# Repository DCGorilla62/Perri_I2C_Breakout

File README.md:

# Perri_I2C_Breakout

Prototype board to connect all Perri boards for testing

Would use OSHPark services to spin this board.

Double copper layer. Black PCB.

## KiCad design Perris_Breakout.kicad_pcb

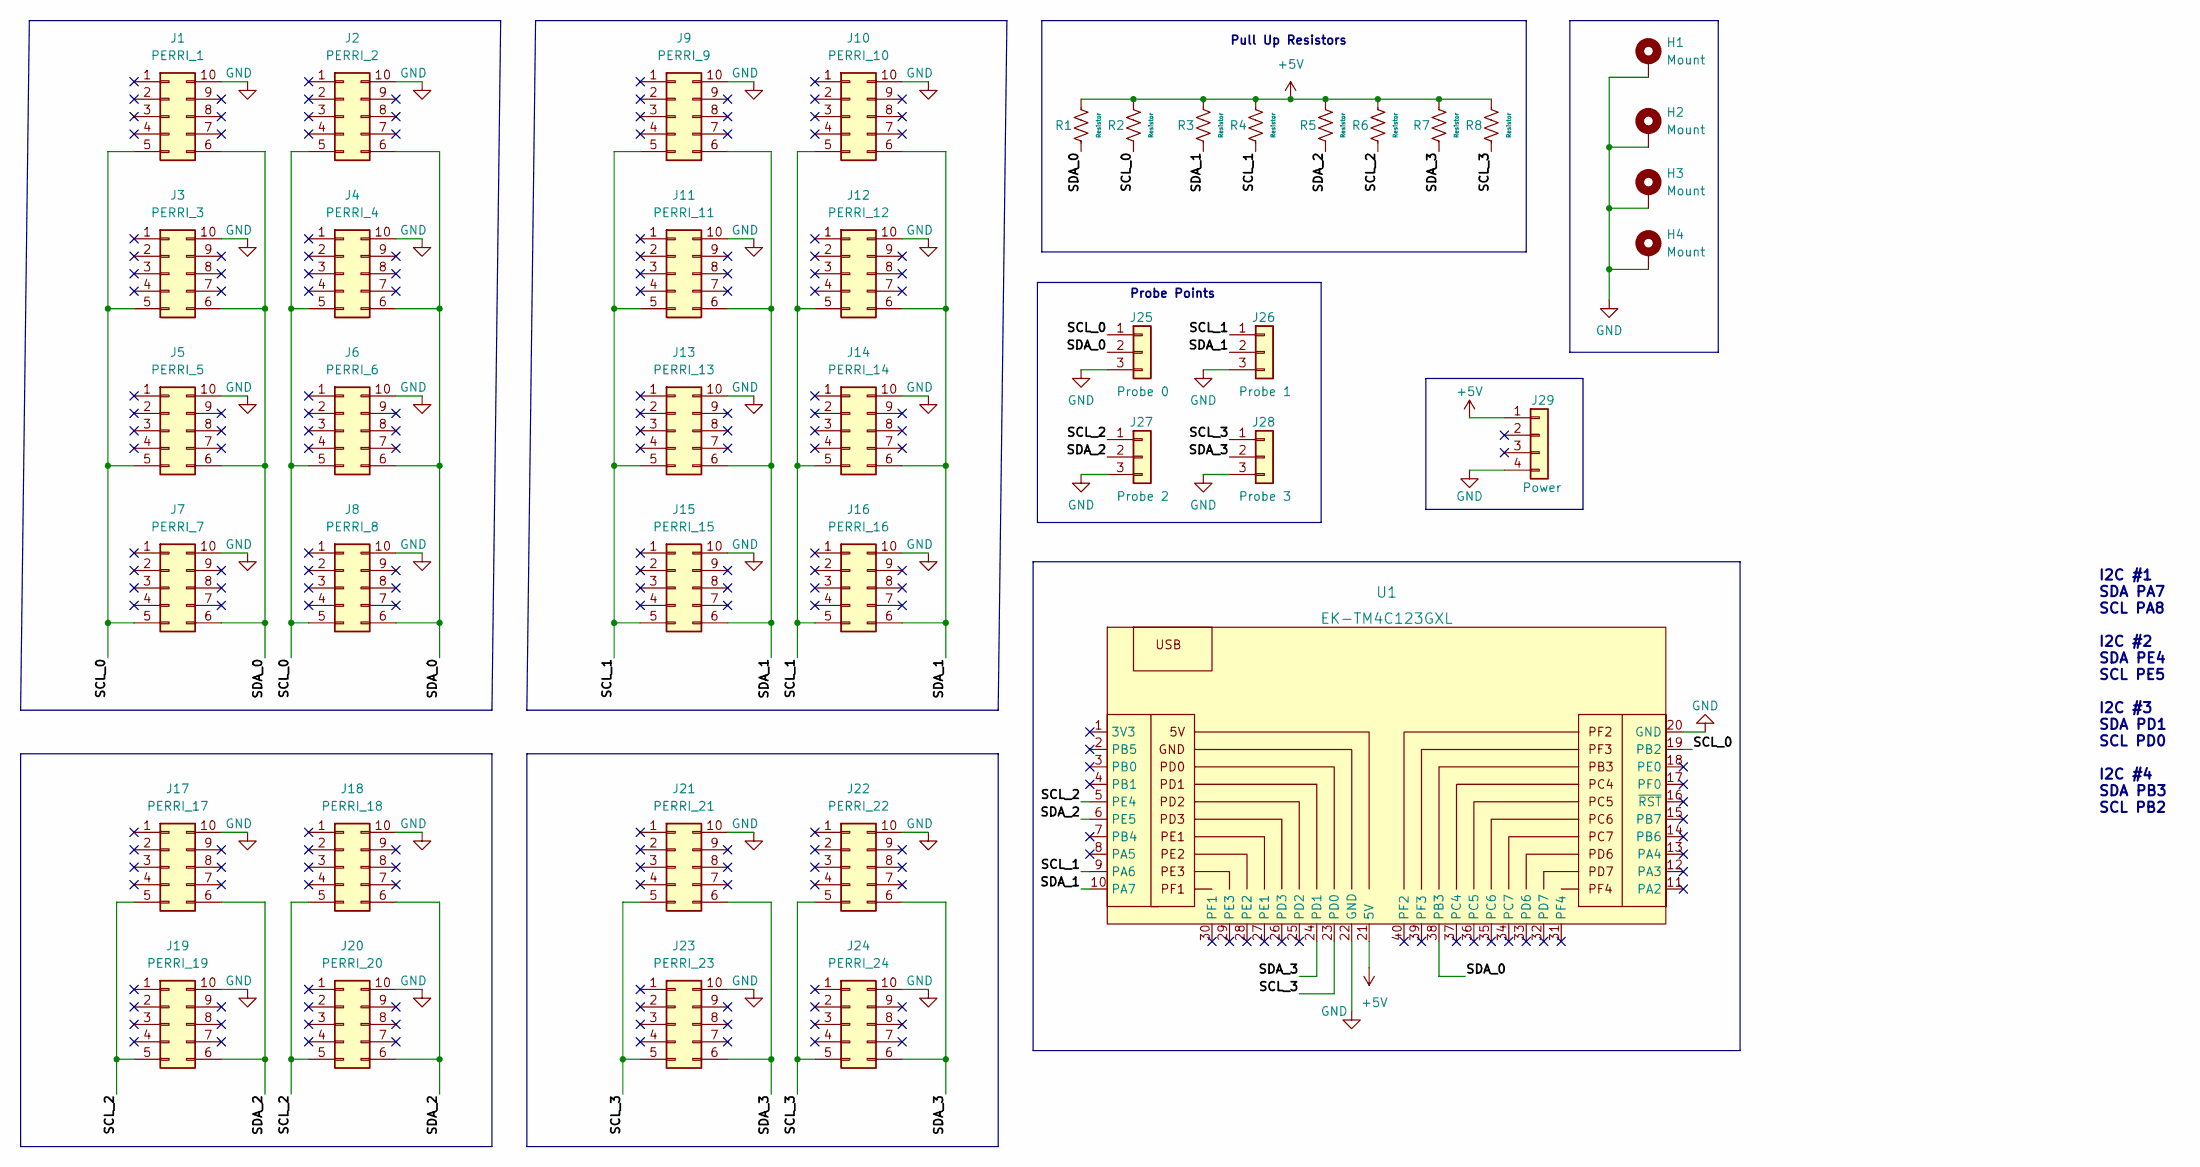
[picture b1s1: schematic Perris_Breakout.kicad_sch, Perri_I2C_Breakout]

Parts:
H1, H2, H3, H4: Mount; MountingHole_3.2mm_M3_ISO7380_Pad
J1: PERRI_1; Perri_conn_2x5_Reverse
J2: PERRI_2; Perri_conn_2x5_Reverse
J3: PERRI_3; Perri_conn_2x5_Reverse
J4: PERRI_4; Perri_conn_2x5_Reverse
J5: PERRI_5; Perri_conn_2x5_Reverse
J6: PERRI_6; Perri_conn_2x5_Reverse
J7: PERRI_7; Perri_conn_2x5_Reverse
J8: PERRI_8; Perri_conn_2x5_Reverse
J9: PERRI_9; Perri_conn_2x5_Reverse
J10: PERRI_10; Perri_conn_2x5_Reverse
J11: PERRI_11; Perri_conn_2x5_Reverse
J12: PERRI_12; Perri_conn_2x5_Reverse
J13: PERRI_13; Perri_conn_2x5_Reverse
J14: PERRI_14; Perri_conn_2x5_Reverse
J15: PERRI_15; Perri_conn_2x5_Reverse
J16: PERRI_16; Perri_conn_2x5_Reverse
J17: PERRI_17; Perri_conn_2x5_Reverse
J18: PERRI_18; Perri_conn_2x5_Reverse
J19: PERRI_19; Perri_conn_2x5_Reverse
J20: PERRI_20; Perri_conn_2x5_Reverse
J21: PERRI_21; Perri_conn_2x5_Reverse
J22: PERRI_22; Perri_conn_2x5_Reverse
J23: PERRI_23; Perri_conn_2x5_Reverse
J24: PERRI_24; Perri_conn_2x5_Reverse
J25: Probe 0; PinHeader_1x03_P2.54mm_Vertical
J26: Probe 1; PinHeader_1x03_P2.54mm_Vertical
J27: Probe 2; PinHeader_1x03_P2.54mm_Vertical
J28: Probe 3; PinHeader_1x03_P2.54mm_Vertical
J29: Power; Molex_Micro-Fit_3.0_43650-0400_1x04_P3.00mm_Horizontal
R1, R2, R3, R4, R5, R6, R7, R8: Resistor; R_0805_2012Metric
U1: EK-TM4C123GXL; TM4C123GXL_launchpad_male_connector; MPN EK-TM4C123GXL

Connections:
+5V: J29.1, R1.2, R2.2, R3.2, R4.2, R5.2, R6.2, R7.2, R8.2, U1.21 (5V)
/SCL_0: J1.5, J2.5, J3.5, J4.5, J5.5, J6.5, J7.5, J8.5, J25.1, R2.1, U1.19 (PB2)
/SCL_1: J9.5, J10.5, J11.5, J12.5, J13.5, J14.5, J15.5, J16.5, J26.1, R4.1, U1.9 (PA6)
/SCL_2: J17.5, J18.5, J19.5, J20.5, J27.1, R6.1, U1.5 (PE4)
/SCL_3: J21.5, J22.5, J23.5, J24.5, J28.1, R8.1, U1.23 (PD0)
/SDA_0: J1.6, J2.6, J3.6, J4.6, J5.6, J6.6, J7.6, J8.6, J25.2, R1.1, U1.38 (PB3)
/SDA_1: J9.6, J10.6, J11.6, J12.6, J13.6, J14.6, J15.6, J16.6, J26.2, R3.1, U1.10 (PA7)
/SDA_2: J17.6, J18.6, J19.6, J20.6, J27.2, R5.1, U1.6 (PE5)
/SDA_3: J21.6, J22.6, J23.6, J24.6, J28.2, R7.1, U1.24 (PD1)
GND: H1.1, H2.1, H3.1, H4.1, J1.10, J2.10, J3.10, J4.10, J5.10, J6.10, J7.10, J8.10, J9.10, J10.10, J11.10, J12.10, J13.10, J14.10, J15.10, J16.10, J17.10, J18.10, J19.10, J20.10, J21.10, J22.10, J23.10, J24.10, J25.3, J26.3, J27.3, J28.3, J29.4, U1.20 (GND), U1.22 (GND)

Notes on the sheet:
Probe Points
Pull Up Resistors
I2C #1 SDA PA7 SCL PA8 I2C #2 SDA PE4 SCL PE5 I2C #3 SDA PD1 SCL PD0 I2C #4 SDA PB3 SCL PB2

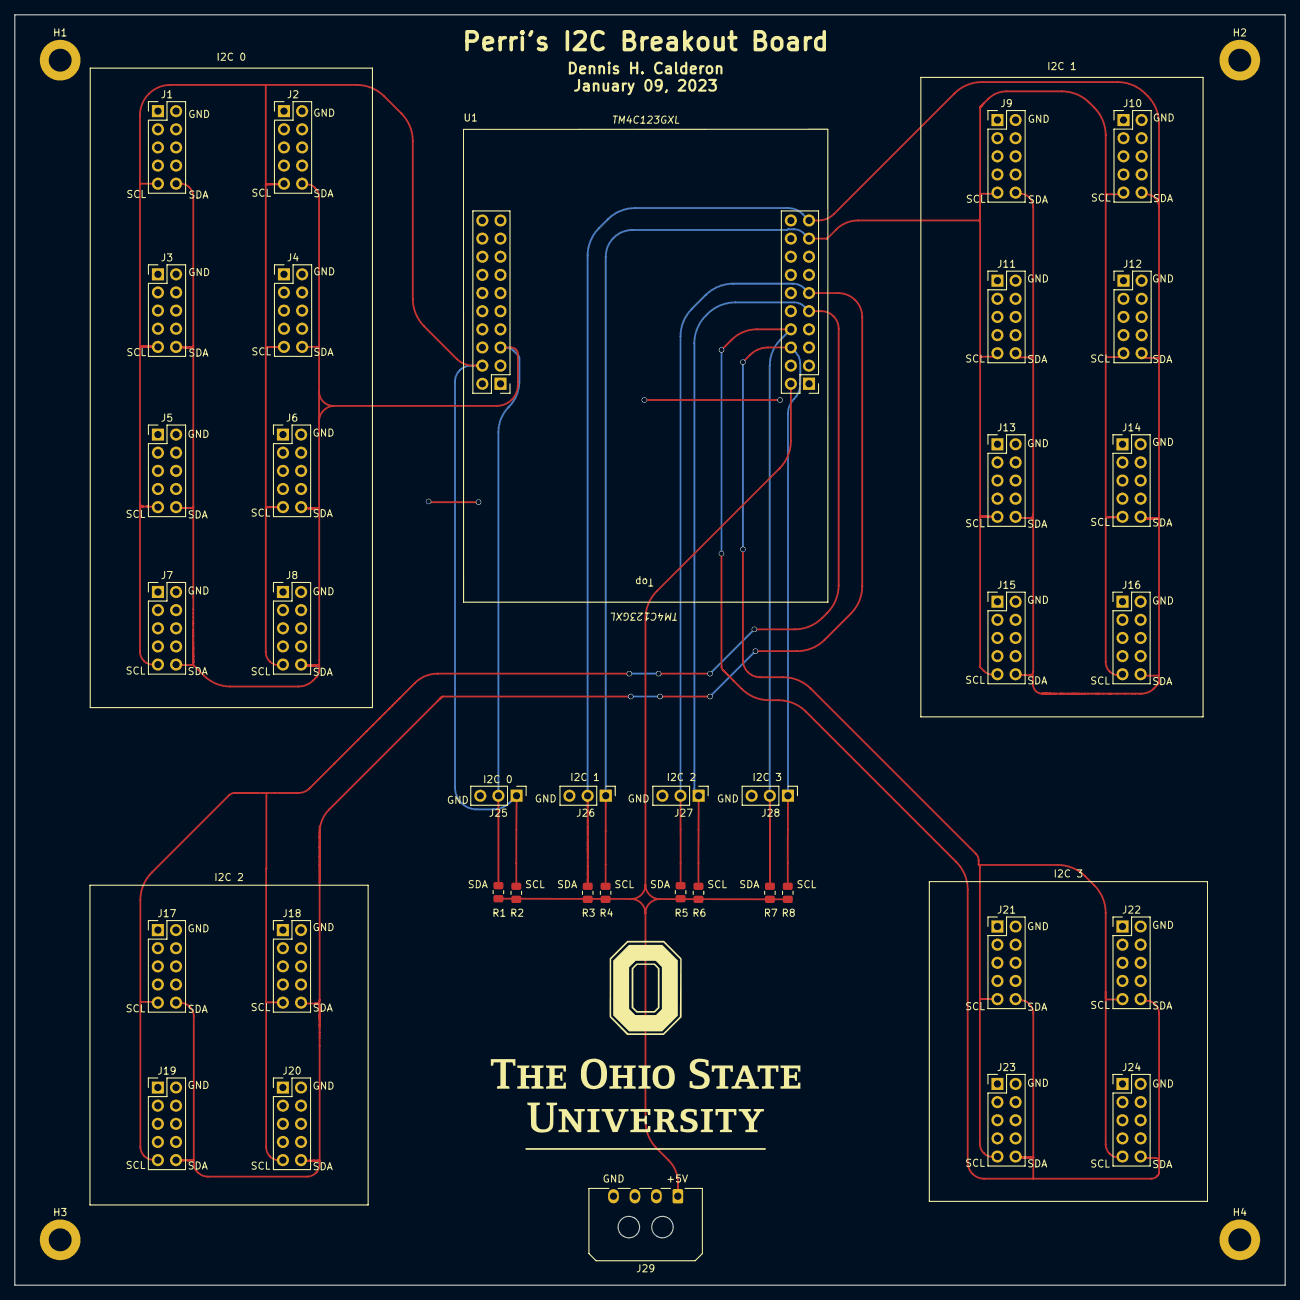
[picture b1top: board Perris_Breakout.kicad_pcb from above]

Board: 2 copper layers, 177.8 x 177.8 mm, 42 parts (0 on the bottom side), 10 nets.

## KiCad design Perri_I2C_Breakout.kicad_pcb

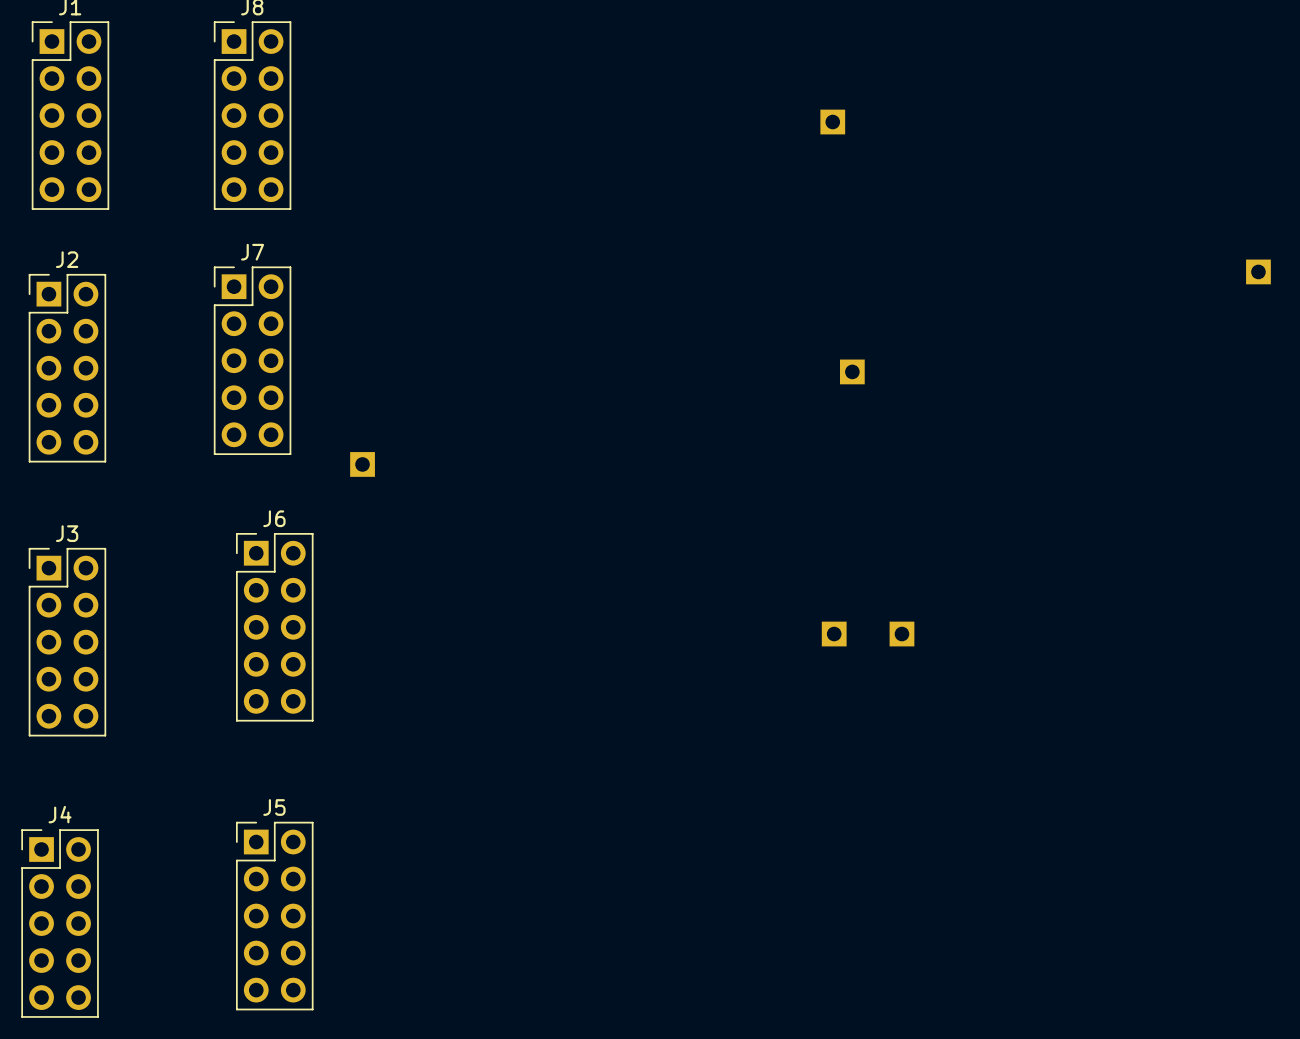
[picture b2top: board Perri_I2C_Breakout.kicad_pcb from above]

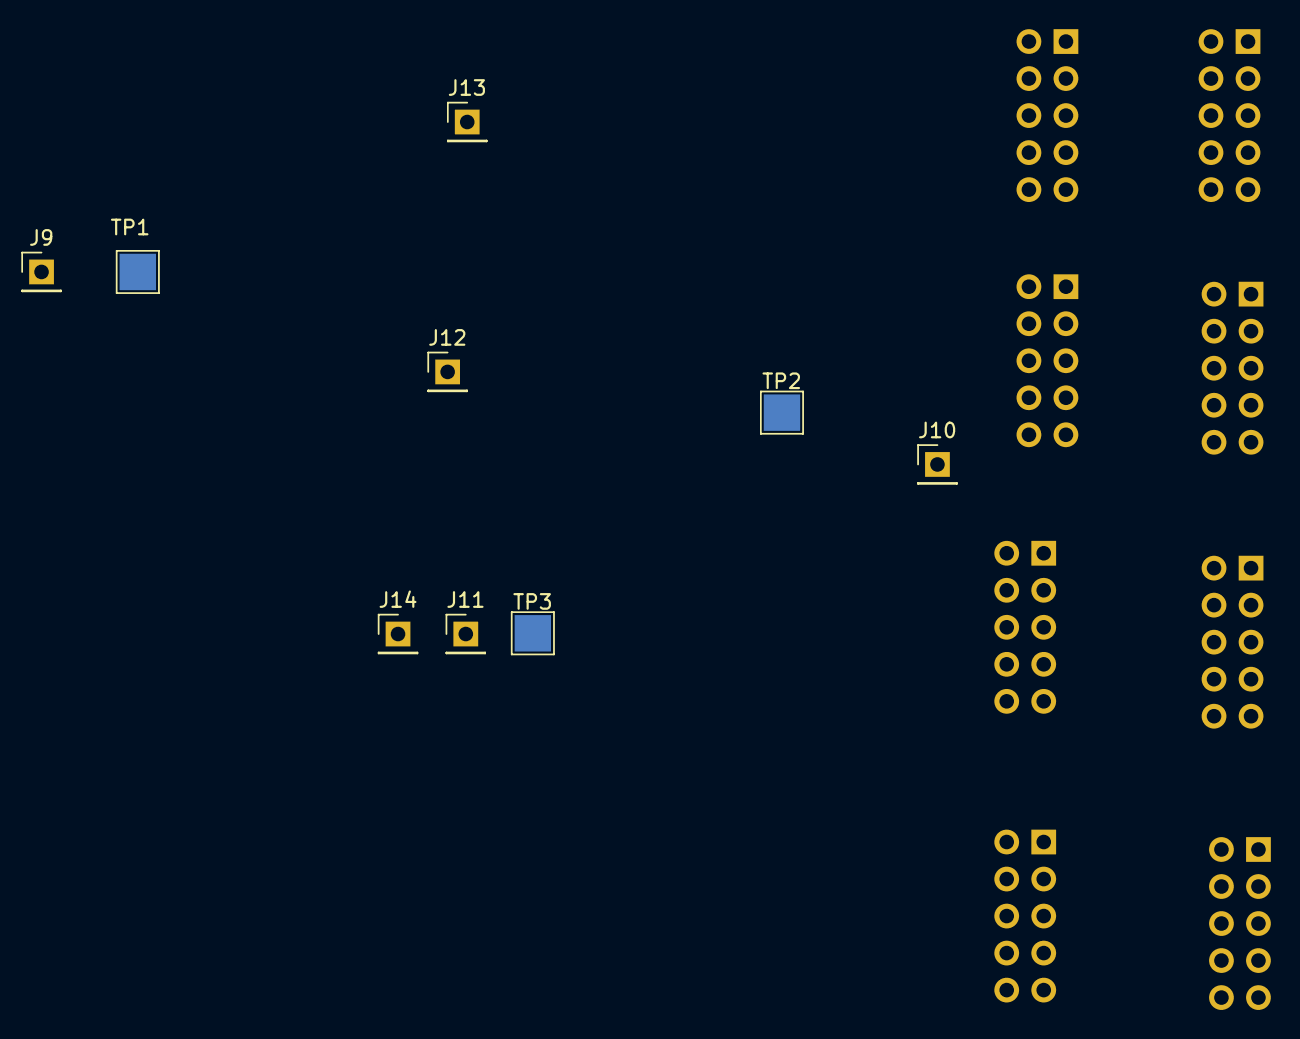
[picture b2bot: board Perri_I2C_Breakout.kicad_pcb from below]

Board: 2 copper layers, 17 parts (9 on the bottom side), 3 nets, no tracks yet.

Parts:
J1: PERRI_1; Perri_conn_2x5
J2: PERRI_2; Perri_conn_2x5
J3: PERRI_3; Perri_conn_2x5
J4: PERRI_4; Perri_conn_2x5
J5: PERRI_5; Perri_conn_2x5
J6: PERRI_6; Perri_conn_2x5
J7: PERRI_7; Perri_conn_2x5
J8: PERRI_8; Perri_conn_2x5
J9, J11, J13: Conn_01x01_Male; PinHeader_1x01_P2.54mm_Vertical
J10, J12, J14: SCL_Microcontroller; PinHeader_1x01_P2.54mm_Vertical
TP1, TP2, TP3: SCL_Test; TestPoint_Pad_2.5x2.5mm

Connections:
/GND: J1.10, J2.10, J3.10, J4.10, J5.10, J6.10, J7.10, J8.10, J13.1, J14.1, TP3.1
/SCL: J1.5, J2.5, J3.5, J4.5, J5.5, J6.5, J7.5, J8.5, J9.1, J10.1, TP1.1
/SDA: J1.6, J2.6, J3.6, J4.6, J5.6, J6.6, J7.6, J8.6, J11.1, J12.1, TP2.1

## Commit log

2022-12-15 Schematic done. PCB in progress
2022-12-16 Finished Perri I2C Breakout Board
2022-12-16 Incresed track width to 50mils. Added vias to connect ground planes.
2022-12-16 Updated PCB with ground plane surroudning connectors.
2022-12-17 Changed copper zone properties
2022-12-17 merged from main
2022-12-17 Added second copper layer for ground
2022-12-19 Updated Schematic to add GND, SCL, SDA nets to unused pins. Upated PCB to add filled copper zones for SDA, SCL, and GND nets. Generated new drill and gerber files
2022-12-20 Added filled zones for SDA and SCL nets
2023-01-06 More Perris
2023-01-07 Finished placin compononets onto PCB.
2023-01-09 Updated silk screens and rearranged components.
2023-01-09 All tracks complete. DRC passed with no errors or warnings.
2023-01-09 Used vias. Took them out anyway.
2023-01-09 Changed footprint for Perri connnector. Used vias. Fixed power connector orientation.
2023-01-09 Added silscreen to backside of board.
2023-01-09 Generated gerber files.
